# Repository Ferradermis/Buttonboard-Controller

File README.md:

# FRC Custom Operator Control Board
## Overview
This project provides a reusable hardware and software ecosystem for rapidly developing game-specific control surfaces for FIRST Robotics Competition (FRC) teams. Inspired by successful world-class teams who have leveraged custom control boards for years, our solution enables any team to quickly create and deploy specialized operator interfaces tailored to each year's unique game challenges.

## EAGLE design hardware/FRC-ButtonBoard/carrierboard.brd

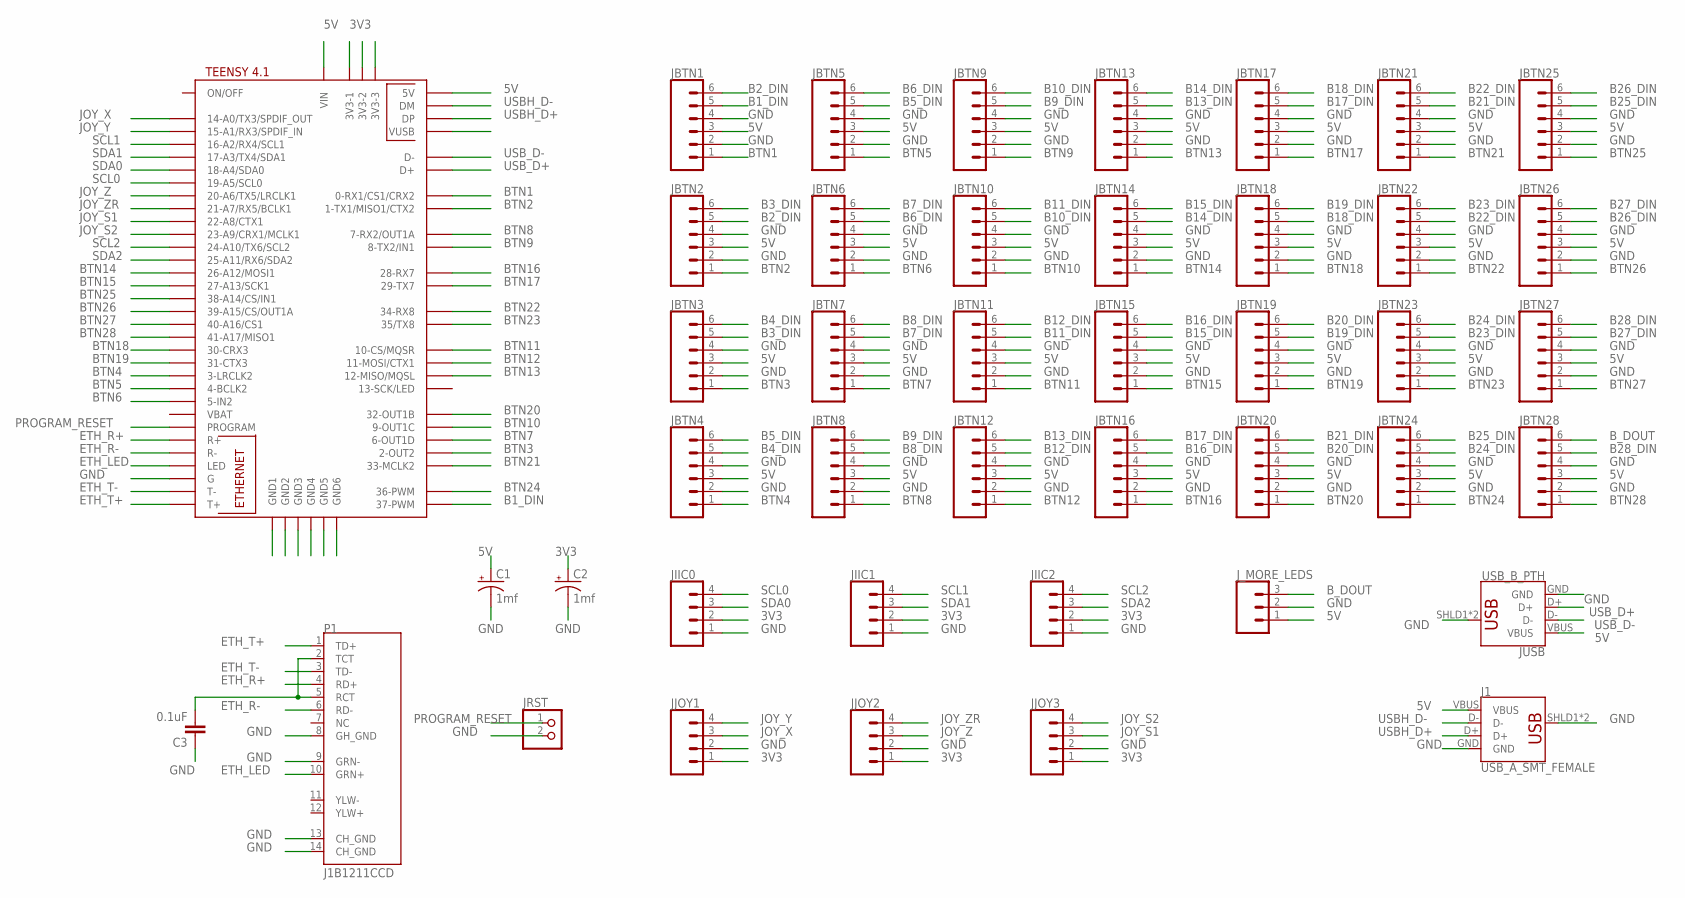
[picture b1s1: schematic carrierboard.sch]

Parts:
C1, C2: 1mf; CPOL-RADIAL-5MM-10MM-KIT
C3: 0.1uF; CAP-PTH-SMALL-KIT
J1: USB_A_SMT_FEMALE; USB-A-S-SILK-FEMALE
JBTN1, JBTN2, JBTN3, JBTN4, JBTN5, JBTN6, JBTN7, JBTN8, JBTN9, JBTN10, JBTN11, JBTN12, JBTN13, JBTN14, JBTN15, JBTN16, JBTN17, JBTN18, JBTN19, JBTN20, JBTN21, JBTN22, JBTN23, JBTN24, JBTN25, JBTN26, JBTN27, JBTN28: CONN_06SILK_FEMALE_PTH; 1X06
JIIC0, JIIC1, JIIC2: CONN_04POLAR; MOLEX-1X4
JJOY1, JJOY2, JJOY3: CONN_04LONGPADS; 1X04_LONGPADS
JRST: PINHD-1X2; 1X02
JUSB: USB_B_PTH; USB-B-PTH
J_MORE_LEDS: CONN_03LONGPADS; 1X03_LONGPADS
P1: J1B1211CCD
U$1: TEENSY41

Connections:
3V3: C2.+, JIIC0.2, JIIC1.2, JIIC2.2, JJOY1.1, JJOY2.1, JJOY3.1, U$1.3V3-1, U$1.3V3-2, U$1.3V3-3
5V: C1.+, J1.VBUS, JBTN1.3, JBTN2.3, JBTN3.3, JBTN4.3, JBTN5.3, JBTN6.3, JBTN7.3, JBTN8.3, JBTN9.3, JBTN10.3, JBTN11.3, JBTN12.3, JBTN13.3, JBTN14.3, JBTN15.3, JBTN16.3, JBTN17.3, JBTN18.3, JBTN19.3, JBTN20.3, JBTN21.3, JBTN22.3, JBTN23.3, JBTN24.3, JBTN25.3, JBTN26.3, JBTN27.3, JBTN28.3, JUSB.VBUS, J_MORE_LEDS.1, U$1.+5V (5V), U$1.VIN
B1_DIN: JBTN1.5, U$1.37-PWM
B2_DIN: JBTN1.6, JBTN2.5
B3_DIN: JBTN2.6, JBTN3.5
B4_DIN: JBTN3.6, JBTN4.5
B5_DIN: JBTN4.6, JBTN5.5
B6_DIN: JBTN5.6, JBTN6.5
B7_DIN: JBTN6.6, JBTN7.5
B8_DIN: JBTN7.6, JBTN8.5
B9_DIN: JBTN8.6, JBTN9.5
B10_DIN: JBTN9.6, JBTN10.5
B11_DIN: JBTN10.6, JBTN11.5
B12_DIN: JBTN11.6, JBTN12.5
B13_DIN: JBTN12.6, JBTN13.5
B14_DIN: JBTN13.6, JBTN14.5
B15_DIN: JBTN14.6, JBTN15.5
B16_DIN: JBTN15.6, JBTN16.5
B17_DIN: JBTN16.6, JBTN17.5
B18_DIN: JBTN17.6, JBTN18.5
B19_DIN: JBTN18.6, JBTN19.5
B20_DIN: JBTN19.6, JBTN20.5
B21_DIN: JBTN20.6, JBTN21.5
B22_DIN: JBTN21.6, JBTN22.5
B23_DIN: JBTN22.6, JBTN23.5
B24_DIN: JBTN23.6, JBTN24.5
B25_DIN: JBTN24.6, JBTN25.5
B26_DIN: JBTN25.6, JBTN26.5
B27_DIN: JBTN26.6, JBTN27.5
B28_DIN: JBTN27.6, JBTN28.5
BTN1: JBTN1.1, U$1.0-RX1/CS1/CRX2
BTN2: JBTN2.1, U$1.1-TX1/MISO1/CTX2
BTN3: JBTN3.1, U$1.2-OUT2
BTN4: JBTN4.1, U$1.3-LRCLK2
BTN5: JBTN5.1, U$1.4-BCLK2
BTN6: JBTN6.1, U$1.5-IN2
BTN7: JBTN7.1, U$1.6-OUT1D
BTN8: JBTN8.1, U$1.7-RX2/OUT1A
BTN9: JBTN9.1, U$1.8-TX2/IN1
BTN10: JBTN10.1, U$1.9-OUT1C
BTN11: JBTN11.1, U$1.10-CS\MQSR (10-CS/MQSR)
BTN12: JBTN12.1, U$1.11-MOSI/CTX1
BTN13: JBTN13.1, U$1.12-MISO/MQSL
BTN14: JBTN14.1, U$1.26-A12/MOSI1
BTN15: JBTN15.1, U$1.27-A13/SCK1
BTN16: JBTN16.1, U$1.28-RX7
BTN17: JBTN17.1, U$1.29-TX7
BTN18: JBTN18.1, U$1.30-CRX3
BTN19: JBTN19.1, U$1.31-CTX3
BTN20: JBTN20.1, U$1.32-OUT1B
BTN21: JBTN21.1, U$1.33-MCLK2
BTN22: JBTN22.1, U$1.34-RX8
BTN23: JBTN23.1, U$1.35-TX8 (35/TX8)
BTN24: JBTN24.1, U$1.36-PWM
BTN25: JBTN25.1, U$1.38-A14/CS/IN1
BTN26: JBTN26.1, U$1.39-A15/CS/OUT1A
BTN27: JBTN27.1, U$1.40-A16/CS1
BTN28: JBTN28.1, U$1.41-A17/MISO1
B_DOUT: JBTN28.6, J_MORE_LEDS.3
ETH_LED: P1.10 (GRN+), U$1.LED
ETH_R+: P1.4 (RD+), U$1.R+
ETH_R-: P1.6 (RD-), U$1.R-
ETH_T+: P1.1 (TD+), U$1.T+
ETH_T-: P1.3 (TD-), U$1.T-
GND: C1.-, C2.-, C3.1, J1.GND, J1.SHLD1 (SHIELD), J1.SHLD2 (SHIELD), JBTN1.2, JBTN1.4, JBTN2.2, JBTN2.4, JBTN3.2, JBTN3.4, JBTN4.2, JBTN4.4, JBTN5.2, JBTN5.4, JBTN6.2, JBTN6.4, JBTN7.2, JBTN7.4, JBTN8.2, JBTN8.4, JBTN9.2, JBTN9.4, JBTN10.2, JBTN10.4, JBTN11.2, JBTN11.4, JBTN12.2, JBTN12.4, JBTN13.2, JBTN13.4, JBTN14.2, JBTN14.4, JBTN15.2, JBTN15.4, JBTN16.2, JBTN16.4, JBTN17.2, JBTN17.4, JBTN18.2, JBTN18.4, JBTN19.2, JBTN19.4, JBTN20.2, JBTN20.4, JBTN21.2, JBTN21.4, JBTN22.2, JBTN22.4, JBTN23.2, JBTN23.4, JBTN24.2, JBTN24.4, JBTN25.2, JBTN25.4, JBTN26.2, JBTN26.4, JBTN27.2, JBTN27.4, JBTN28.2, JBTN28.4, JIIC0.1, JIIC1.1, JIIC2.1, JJOY1.2, JJOY2.2, JJOY3.2, JRST.2, JUSB.GND, JUSB.SHLD1 (SHIELD), JUSB.SHLD2 (SHIELD), J_MORE_LEDS.2, P1.8 (GH_GND), P1.9 (GRN-), P1.13 (CH_GND), P1.14 (CH_GND), U$1.G, U$1.GND1, U$1.GND2, U$1.GND3, U$1.GND4, U$1.GND5, U$1.GND6
JOY_S1: JJOY3.3, U$1.22-A8/CTX1
JOY_S2: JJOY3.4, U$1.23-A9/CRX1/MCLK1
JOY_X: JJOY1.3, U$1.14-A0/TX3/SPDIF_OUT
JOY_Y: JJOY1.4, U$1.15-A1/RX3/SPDIF_IN
JOY_Z: JJOY2.3, U$1.20-A6/TX5/LRCLK1
JOY_ZR: JJOY2.4, U$1.21-A7/RX5/BCLK1
unnamed: C3.2, P1.2 (TCT), P1.5 (RCT)
PROGRAM_RESET: JRST.1, U$1.PROGRAM
SCL0: JIIC0.4, U$1.19-A5/SCL0
SCL1: JIIC1.4, U$1.16-A2/RX4/SCL1
SCL2: JIIC2.4, U$1.24-A10/TX6/SCL2
SDA0: JIIC0.3, U$1.18-A4/SDA0
SDA1: JIIC1.3, U$1.17-A3/TX4/SDA1
SDA2: JIIC2.3, U$1.25-A11/RX6/SDA2
USBH_D+: J1.D+, U$1.DP
USBH_D-: J1.D-, U$1.DM
USB_D+: JUSB.D+, U$1.D+
USB_D-: JUSB.D-, U$1.D-

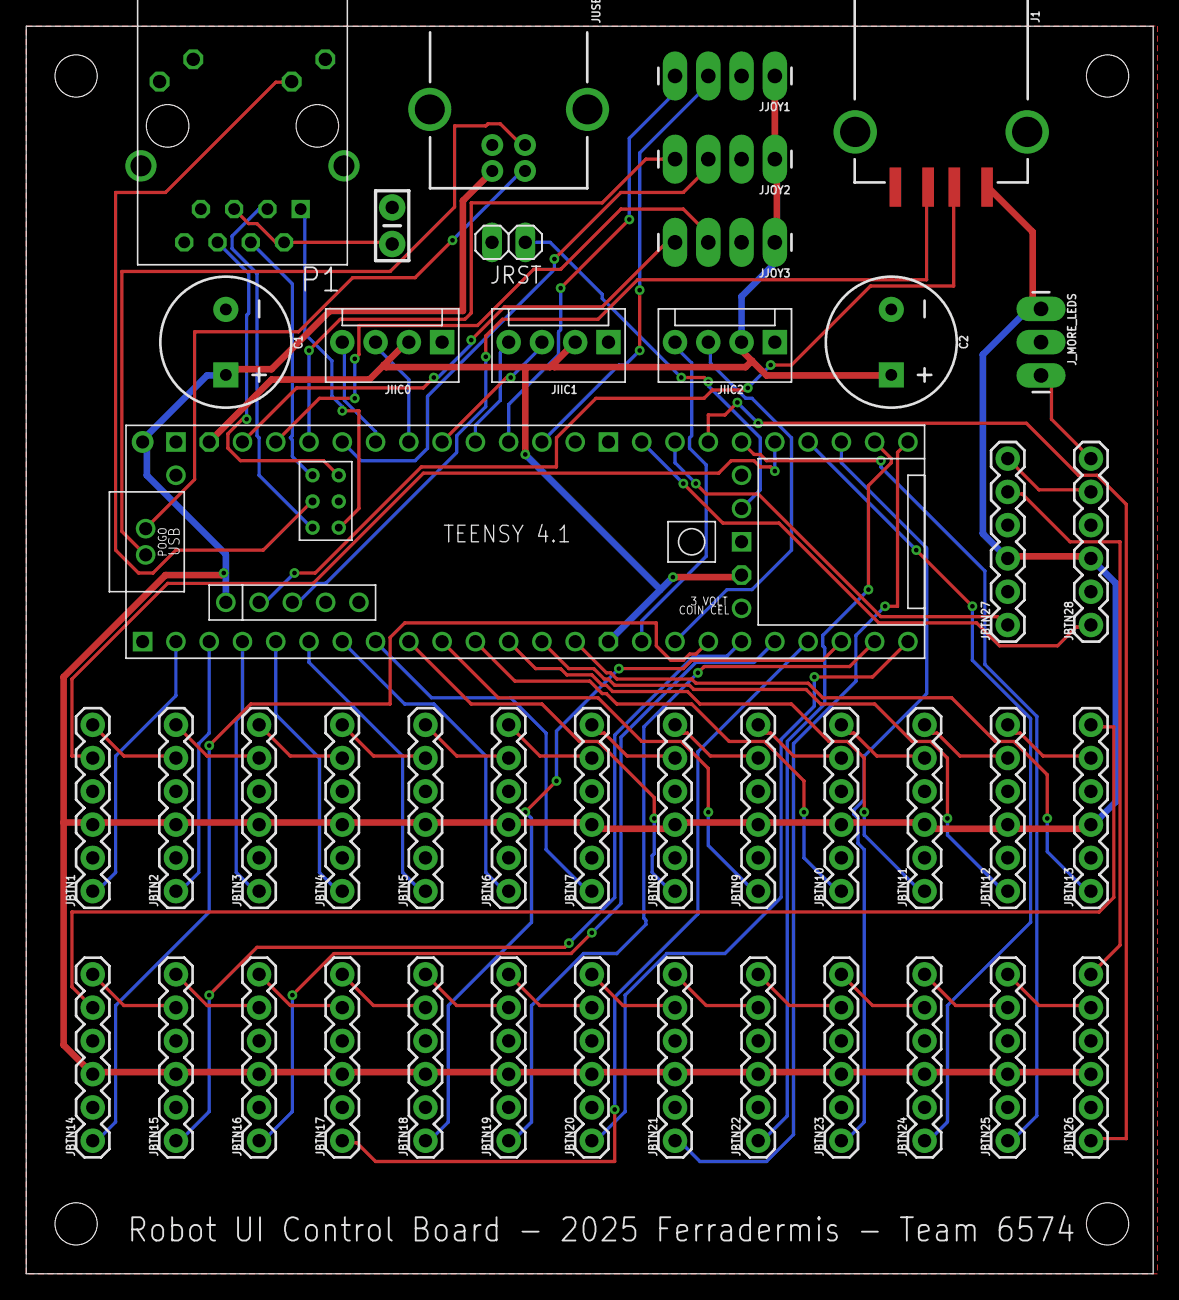
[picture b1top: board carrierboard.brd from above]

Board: 2 copper layers, 86.0 x 95.2 mm, 43 parts (0 on the bottom side), 83 nets.

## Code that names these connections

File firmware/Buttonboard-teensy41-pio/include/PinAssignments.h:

#ifndef PIN_ASSIGNMENTS_H
#define PIN_ASSIGNMENTS_H

// Button Pins
#define PIN_BTN_01 0
#define PIN_BTN_02 1
#define PIN_BTN_03 2
#define PIN_BTN_04 3
#define PIN_BTN_05 4
#define PIN_BTN_06 5
#define PIN_BTN_07 6
#define PIN_BTN_08 7
#define PIN_BTN_09 8
#define PIN_BTN_10 9
#define PIN_BTN_11 10
#define PIN_BTN_12 11
#define PIN_BTN_13 12
#define PIN_BTN_14 26
#define PIN_BTN_15 27
#define PIN_BTN_16 28
#define PIN_BTN_17 29
#define PIN_BTN_18 30
#define PIN_BTN_19 31
#define PIN_BTN_20 32
#define PIN_BTN_21 33
#define PIN_BTN_22 34
#define PIN_BTN_23 35
#define PIN_BTN_24 36
#define PIN_BTN_25 38
#define PIN_BTN_26 39
#define PIN_BTN_27 40
#define PIN_BTN_28 41

// NeoPixel Data Pin
#define DATA_PIN 37

// Joystick Axis Pins
#define PIN_JOY_X 14
#define PIN_JOY_Y 15
#define PIN_JOY_Z 20
#define PIN_JOY_ZR 21
#define PIN_JOY_S1 22
#define PIN_JOY_S2 23

#endif // PIN_ASSIGNMENTS_H

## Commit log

2025-06-29 led test and debounce sketch
2025-06-30 switched connectors to JST HX
2025-07-01 Added FRCNetworkTables class
2025-07-01 implementation and fixed formatIPAddress
2025-07-01 about to merge
2025-07-01 added todo workitems
2025-07-02 commit to more buttons
2025-07-05 code for 4 more buttons and networktables
2025-07-05 buttons
2025-07-08 checking ownership transfer
2025-07-08 pixel pin correction
2025-07-08 button mods
2025-07-08 created platformio project
2025-07-08 create regions for #define directives
2025-07-08 archived arduino .ino project
2025-07-08 playing around with nt
2025-07-08 Update main.cpp - rename PIN_LEDS to PIN_NEOPIXELS
2025-07-12 button tweaks and new printable buttons
2025-07-12 button features and tweaks
2025-07-12 fins on housing and printability changes
2025-07-14 a bit more yet
2025-07-15 working project with buttons
2025-07-17 adjustments for new momentary switches, joystick button states for initial integration with robot
2025-07-17 simplified button housing
2025-07-18 reef colors, joystick class tested
2025-07-19 led cap tweaks
2025-07-19 merged
2025-07-20 button groupings
2025-07-22 pretty initialization of leds
2025-07-26 updated button colors
2025-07-28 button color changes at MROC
2025-08-03 minor changes to dimensions for bambu p1s
2025-08-05 Weekly changes
2025-08-11 NT second attempt
2025-08-12 L1-L4 in their own group
2025-08-13 NT library attempt 3
2025-08-14 much NT Troubleshooting
2025-08-17 UDPServer works. Time to merge in buttons and lights again.
2025-08-17 SO many changes, cleanup, animation management
2025-08-18 warning if button pressed and not teleop
2025-08-18 less chatty driver station log
2025-08-19 match time and pdp voltage
2025-09-15 detect countdown
2025-10-07 respond to tag messages, not working
2025-10-12 game day changes
2025-10-12 catch up button changes
2025-10-13 trying like heck to not block when ethernet is unplugged
2025-10-14 modularize lcd provision
2025-10-28 led caps 2mm higher
2025-10-28 printed them too
2026-03-14 Button mounts for ChromaTek RGB buttons
2026-03-16 ChromaTek button housings
2026-03-22 new animation
2026-03-26 refactored pin assignments
2026-03-26 added brightness sine timer

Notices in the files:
parts and their libraries:
SparkFun-Connectors: Licensing: Creative Commons ShareAlike 4.0 International - https://creativecommons.org/licenses/by-sa/4.0
